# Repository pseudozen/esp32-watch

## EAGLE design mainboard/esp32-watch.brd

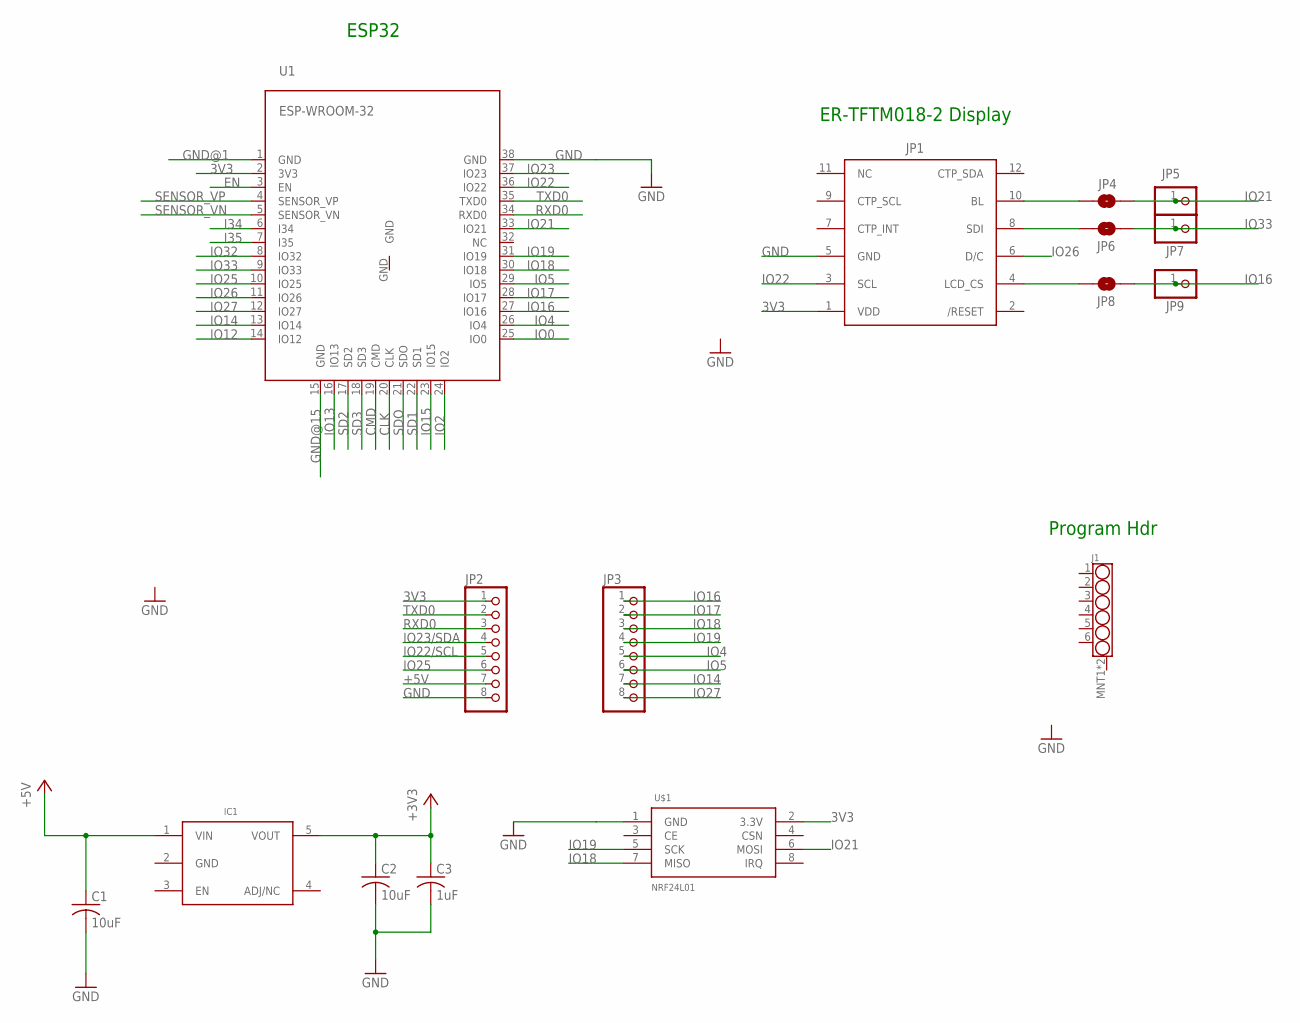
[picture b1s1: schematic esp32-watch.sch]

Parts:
C1, C2: 10uF; C0805
C3: 1uF; C0805
IC1: AP2112-3.3; SOT23-5L
J1: CON-MOLEX_0532610671
JP1: ER-TFTM018-2; ER-TFTM018-2-PTH
JP2, JP3: PINHD-1X8BIG; 1X08-BIG
JP4, JP6, JP8: JUMPER-SMT_2_NO_NO-SILK; SMT-JUMPER_2_NO_NO-SILK
JP5, JP7, JP9: PINHD-1X1; 1X01
U1: ESP-WROOM-32
U$1: NRF24L01; NRF24L01-MODULE

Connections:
3V3: JP1.1 (VDD), JP2.1, U1.2 (3V3), U$1.2 (3.3V)
+3V3: C2.1, C3.1, IC1.5 (VOUT)
+5V: C1.1, IC1.1 (VIN), JP2.7
CLK: U1.20 (CLK)
CMD: U1.19 (CMD)
EN: U1.3 (EN)
GND: C1.2, C2.2, C3.2, IC1.2 (GND), JP1.5 (GND), JP2.8, U1.38 (GND), U$1.1 (GND)
GND@1: U1.1 (GND)
GND@15: U1.15 (GND)
I34: U1.6 (I34)
I35: U1.7 (I35)
IO0: U1.25 (IO0)
IO2: U1.24 (IO2)
IO4: JP3.5, U1.26 (IO4)
IO5: JP3.6, U1.29 (IO5)
IO12: U1.14 (IO12)
IO13: U1.16 (IO13)
IO14: JP3.7, U1.13 (IO14)
IO15: U1.23 (IO15)
IO16: JP3.1, JP8.2, JP9.1, U1.27 (IO16)
IO17: JP3.2, U1.28 (IO17)
IO18: JP3.3, U1.30 (IO18), U$1.7 (MISO)
IO19: JP3.4, U1.31 (IO19), U$1.5 (SCK)
IO21: JP4.2, JP5.1, U1.33 (IO21), U$1.6 (MOSI)
IO22: JP1.3 (SCL), U1.36 (IO22)
IO22/SCL: JP2.5
IO23: U1.37 (IO23)
IO23/SDA: JP2.4
IO25: JP2.6, U1.10 (IO25)
IO26: JP1.6 (D/C), U1.11 (IO26)
IO27: JP3.8, U1.12 (IO27)
IO32: U1.8 (IO32)
IO33: JP6.2, JP7.1, U1.9 (IO33)
unnamed: JP1.10 (BL), JP4.1
unnamed: JP1.8 (SDI), JP6.1
unnamed: JP1.4 (LCD_CS), JP8.1
RXD0: JP2.3, U1.34 (RXD0)
SD1: U1.22 (SD1)
SD2: U1.17 (SD2)
SD3: U1.18 (SD3)
SDO: U1.21 (SDO)
SENSOR_VN: U1.5 (SENSOR_VN)
SENSOR_VP: U1.4 (SENSOR_VP)
TXD0: JP2.2, U1.35 (TXD0)

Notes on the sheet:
ER-TFTM018-2 Display
ESP32
Program Hdr

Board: 2 copper layers, 16 parts (0 on the bottom side), 22 nets, no tracks yet.

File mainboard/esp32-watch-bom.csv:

"Qty";"Value";"Device";"Package";"Parts";"Description";"DIGIKEY";"MFR";"MPN";
"1";"";"AP2112-3.3";"SOT23-5L";"IC1";"";"";"";"";
"1";"";"ER-TFTM018-2";"ER-TFTM018-2-PTH";"JP1";"1.8" SPI 128x160 TFT Touch Screen LCD Module from BuyDisplay";"";"";"";
"3";"";"PINHD-1X1";"1X01";"JP5, JP7, JP9";"Pin header 1x1 for 0.1" spacing";"";"";"";
"2";"";"PINHD-1X8BIG";"1X08-BIG";"JP2, JP3";"PIN HEADER";"";"";"";
"2";"10uF";"C-USC0805";"C0805";"C1, C2";"CAPACITOR, American symbol";"";"";"";
"1";"1uF";"C-USC0805";"C0805";"C3";"CAPACITOR, American symbol";"";"";"";
"1";"CON-MOLEX_0532610671";"CON-MOLEX_0532610671";"CON-MOLEX_0532610671";"J1";"Molex: 6 pin 1.25mm Right Angle SMD connector";"WM7624CT-ND";"Molex";"0532610671";
"1";"ESP-WROOM-32";"ESP-WROOM-32";"ESP-WROOM-32";"U1";"";"";"";"";
"3";"JUMPER-SMT_2_NO_NO-SILK";"JUMPER-SMT_2_NO_NO-SILK";"SMT-JUMPER_2_NO_NO-SILK";"JP4, JP6, JP8";"Normally open jumper";"";"";"";

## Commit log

2018-09-20 initial board layout and auto-route
2018-09-20 added gitignore
2018-09-20 added schematic
2018-10-10 started to add NRF24L01 header
